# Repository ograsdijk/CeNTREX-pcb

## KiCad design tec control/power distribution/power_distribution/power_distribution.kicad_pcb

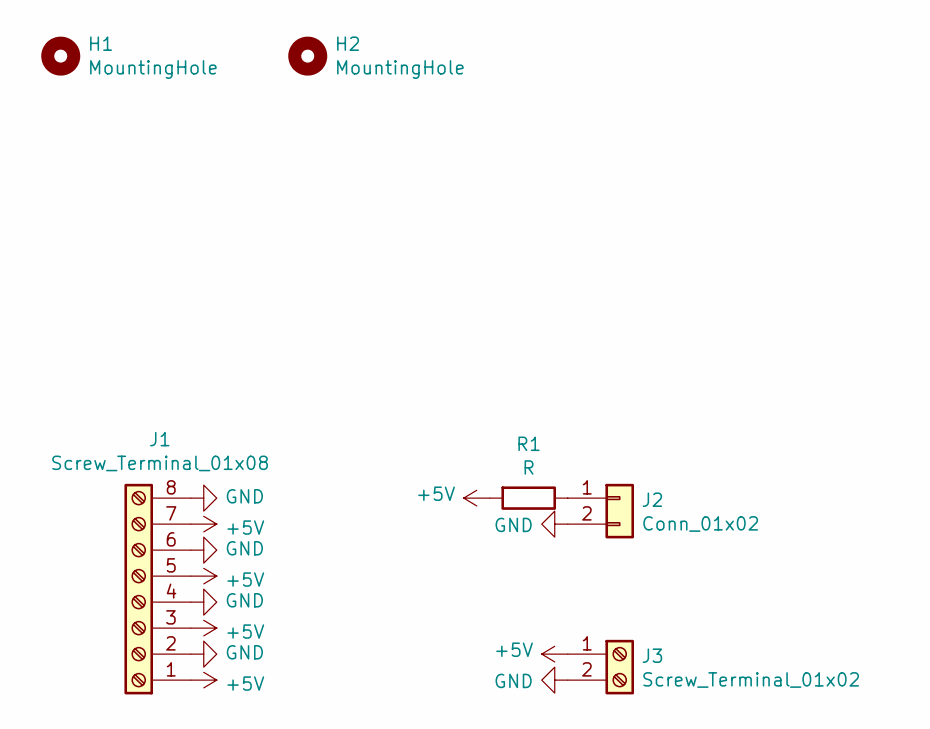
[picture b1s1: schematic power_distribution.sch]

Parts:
H1, H2: MountingHole; MountingHole_2.7mm_M2.5_Pad_Via
J1: Screw_Terminal_01x08; TerminalBlock_RND_205-00018_1x08_P5.00mm_Horizontal
J2: Conn_01x02; PinHeader_1x02_P2.54mm_Vertical
J3: Screw_Terminal_01x02; TerminalBlock_RND_205-00001_1x02_P5.00mm_Horizontal
R1: R; R_Axial_DIN0207_L6.3mm_D2.5mm_P7.62mm_Horizontal

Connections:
+5V: J1.1, J1.3, J1.5, J1.7, J3.1, R1.2
GND: J1.2, J1.4, J1.6, J1.8, J2.2, J3.2
unnamed: J2.1, R1.1

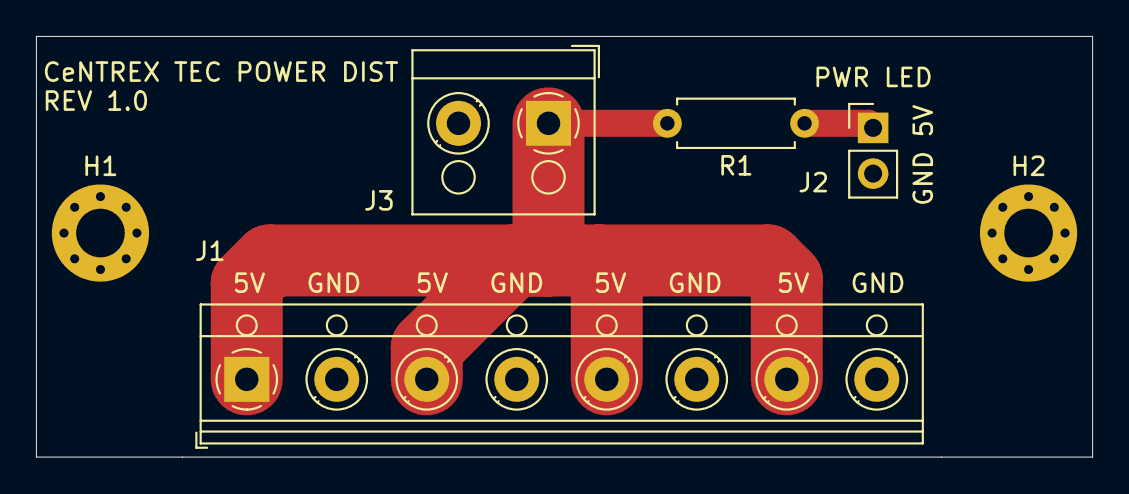
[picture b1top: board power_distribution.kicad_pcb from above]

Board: 2 copper layers, 58.7 x 23.4 mm, 6 parts (0 on the bottom side), 3 nets.

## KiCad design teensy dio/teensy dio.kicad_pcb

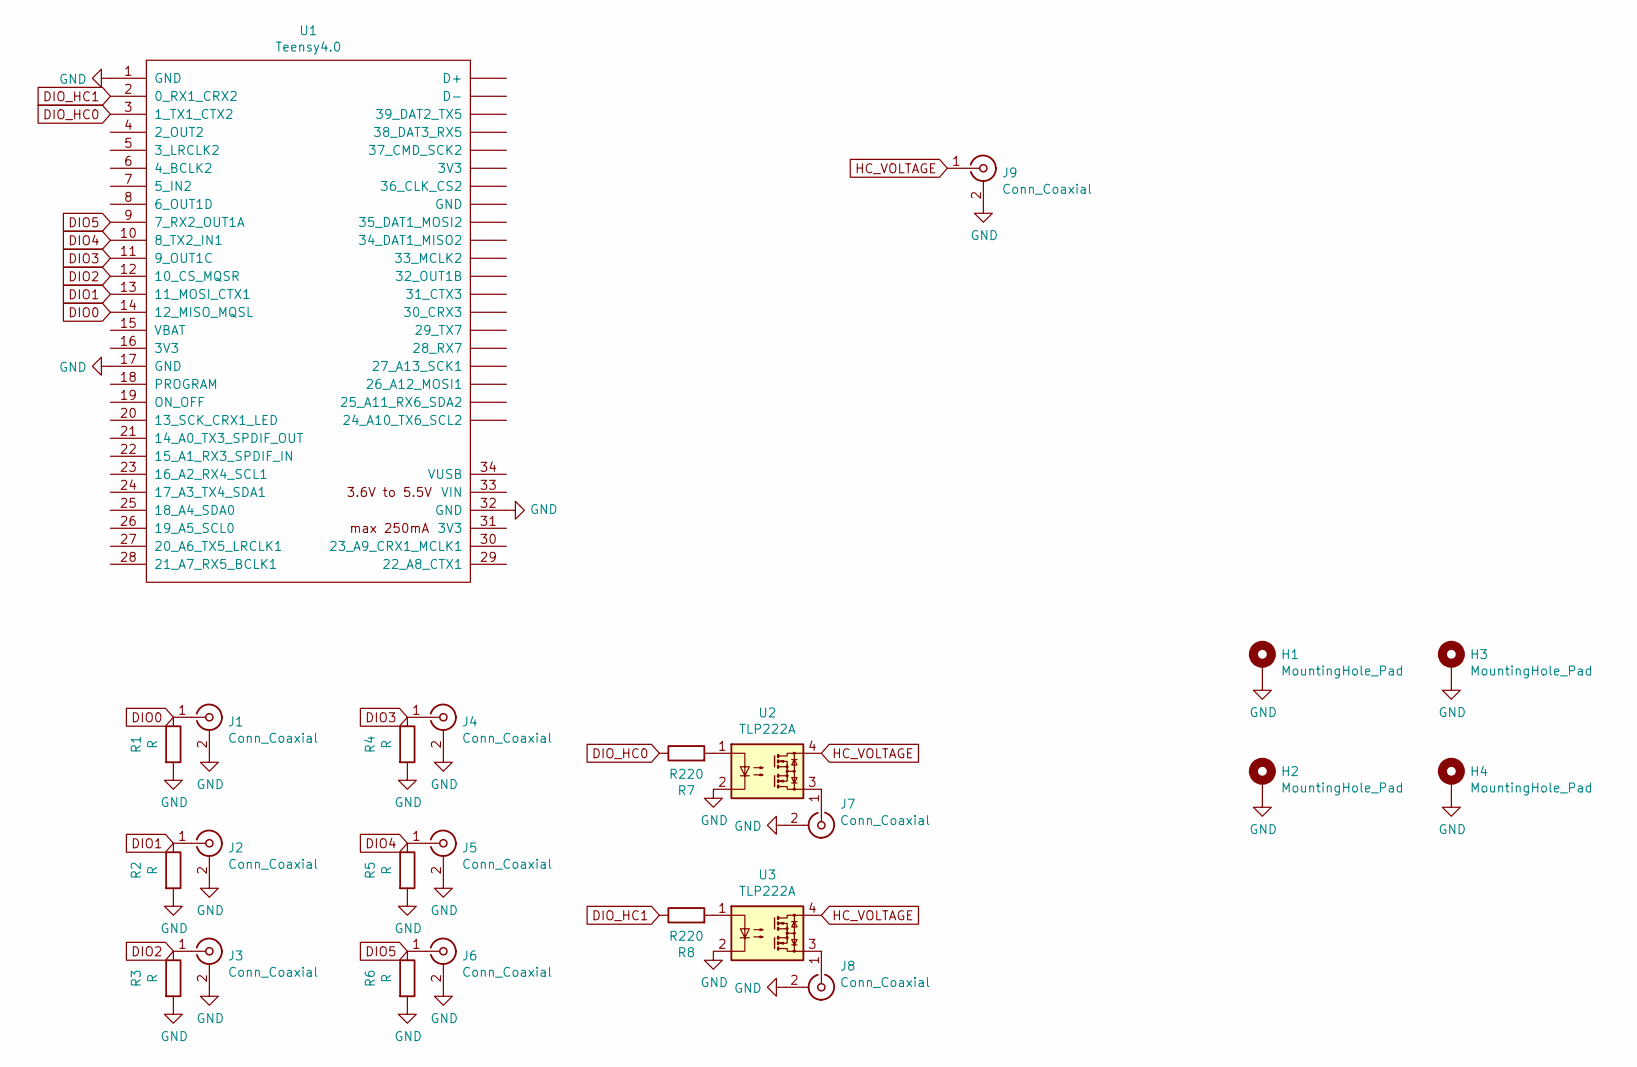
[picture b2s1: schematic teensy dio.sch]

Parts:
H1, H2, H3, H4: MountingHole_Pad; MountingHole_3.2mm_M3_Pad_Via
J1, J2, J3, J4, J5, J6, J7, J8, J9: Conn_Coaxial; BNC_Amphenol_B6252HB-NPP3G-50_Horizontal
R1, R2, R3, R4, R5, R6: R; R_0805_2012Metric
R7, R8: R220; R_0805_2012Metric
U1: Teensy4.0; Teensy40
U2, U3: TLP222A; DIP-4_W7.62mm

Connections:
DIO0: J1.1 (In), R1.1, U1.14 (12_MISO_MQSL)
DIO1: J2.1 (In), R2.1, U1.13 (11_MOSI_CTX1)
DIO2: J3.1 (In), R3.1, U1.12 (10_CS_MQSR)
DIO3: J4.1 (In), R4.1, U1.11 (9_OUT1C)
DIO4: J5.1 (In), R5.1, U1.10 (8_TX2_IN1)
DIO5: J6.1 (In), R6.1, U1.9 (7_RX2_OUT1A)
DIO_HC0: R7.1, U1.3 (1_TX1_CTX2)
DIO_HC1: R8.1, U1.2 (0_RX1_CRX2)
GND: H1.1, H2.1, H3.1, H4.1, J1.2 (Ext), J2.2 (Ext), J3.2 (Ext), J4.2 (Ext), J5.2 (Ext), J6.2 (Ext), J7.2 (Ext), J8.2 (Ext), J9.2 (Ext), R1.2, R2.2, R3.2, R4.2, R5.2, R6.2, U1.1 (GND), U1.17 (GND), U1.32 (GND), U2.2, U3.2
HC_VOLTAGE: J9.1 (In), U2.4, U3.4
unnamed: J7.1 (In), U2.3
unnamed: J8.1 (In), U3.3
unnamed: R7.2, U2.1
unnamed: R8.2, U3.1

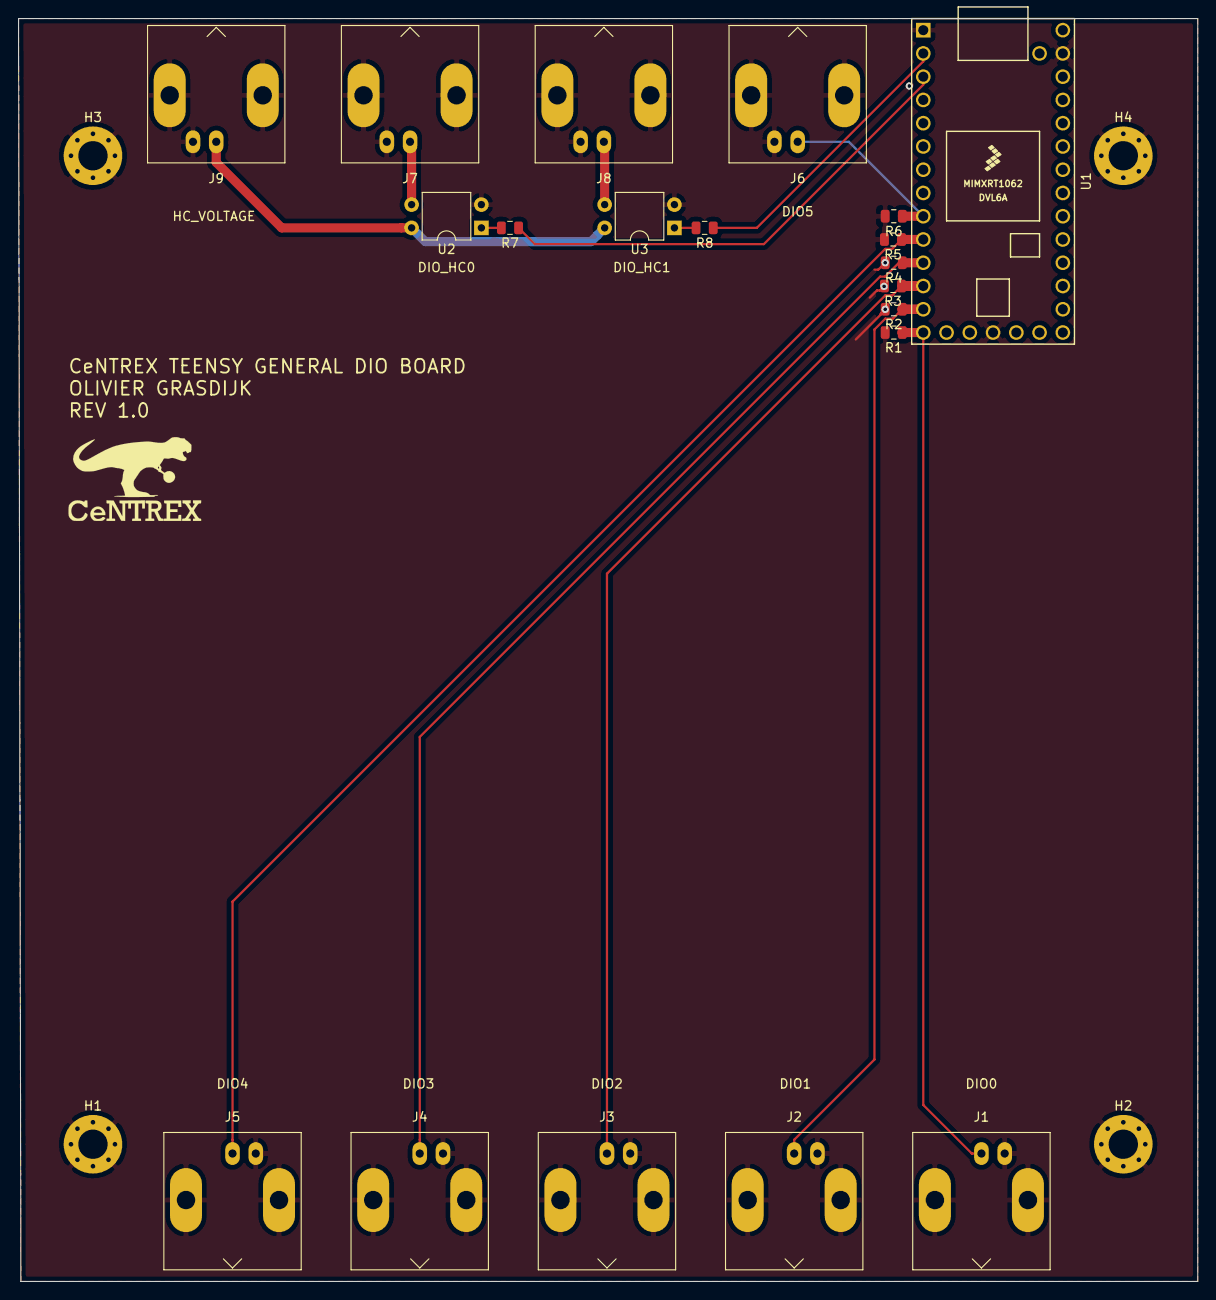
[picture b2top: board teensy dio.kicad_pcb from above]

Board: 2 copper layers, 128.8 x 137.9 mm, 24 parts (0 on the bottom side), 14 nets.

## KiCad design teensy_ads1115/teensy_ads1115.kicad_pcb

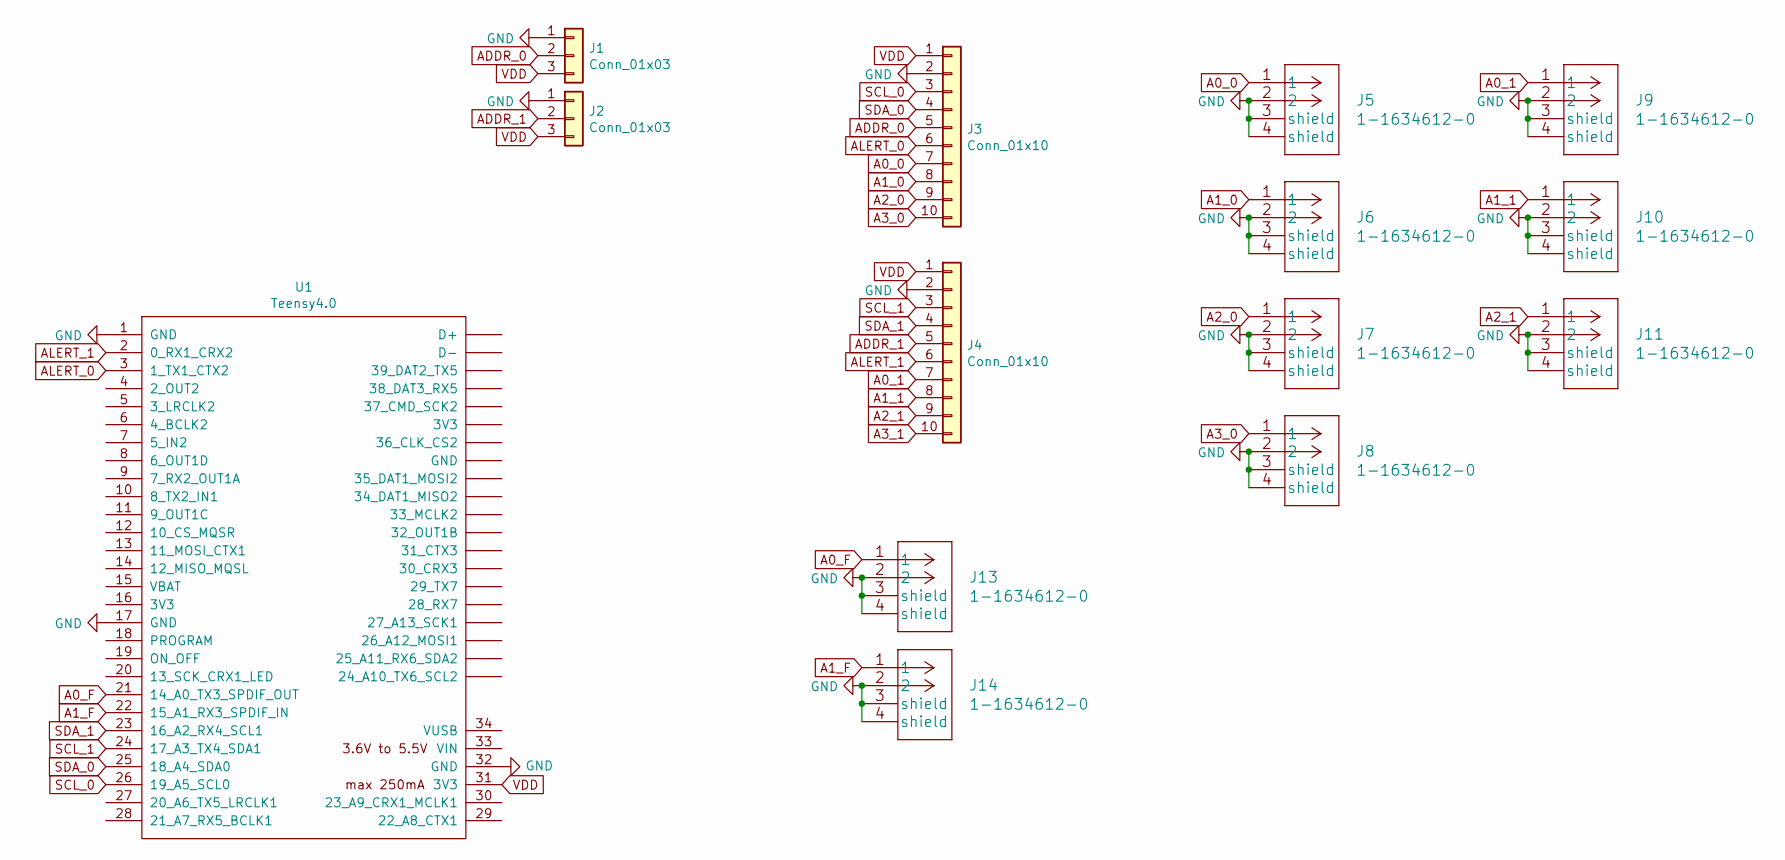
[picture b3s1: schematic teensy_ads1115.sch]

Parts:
J1, J2: Conn_01x03; PinHeader_1x03_P2.54mm_Vertical
J3, J4: Conn_01x10; PinHeader_1x10_P2.54mm_Vertical
J5, J6, J7, J8, J9, J10, J11, J13, J14: 1-1634612-0
U1: Teensy4.0; Teensy40

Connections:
A0_0: J3.7, J5.1
A0_1: J4.7, J9.1
A0_F: J13.1, U1.21 (14_A0_TX3_SPDIF_OUT)
A1_0: J3.8, J6.1
A1_1: J4.8, J10.1
A1_F: J14.1, U1.22 (15_A1_RX3_SPDIF_IN)
A2_0: J3.9, J7.1
A2_1: J4.9, J11.1
A3_0: J3.10, J8.1
A3_1: J4.10
ADDR_0: J1.2, J3.5
ADDR_1: J2.2, J4.5
ALERT_0: J3.6, U1.3 (1_TX1_CTX2)
ALERT_1: J4.6, U1.2 (0_RX1_CRX2)
GND: J1.1, J2.1, J3.2, J4.2, J5.2, J5.3 (shield), J5.4 (shield), J6.2, J6.3 (shield), J6.4 (shield), J7.2, J7.3 (shield), J7.4 (shield), J8.2, J8.3 (shield), J8.4 (shield), J9.2, J9.3 (shield), J9.4 (shield), J10.2, J10.3 (shield), J10.4 (shield), J11.2, J11.3 (shield), J11.4 (shield), J13.2, J13.3 (shield), J13.4 (shield), J14.2, J14.3 (shield), J14.4 (shield), U1.1 (GND), U1.17 (GND), U1.32 (GND)
SCL_0: J3.3, U1.26 (19_A5_SCL0)
SCL_1: J4.3, U1.24 (17_A3_TX4_SDA1)
SDA_0: J3.4, U1.25 (18_A4_SDA0)
SDA_1: J4.4, U1.23 (16_A2_RX4_SCL1)
VDD: J1.3, J2.3, J3.1, J4.1, U1.31 (3V3)

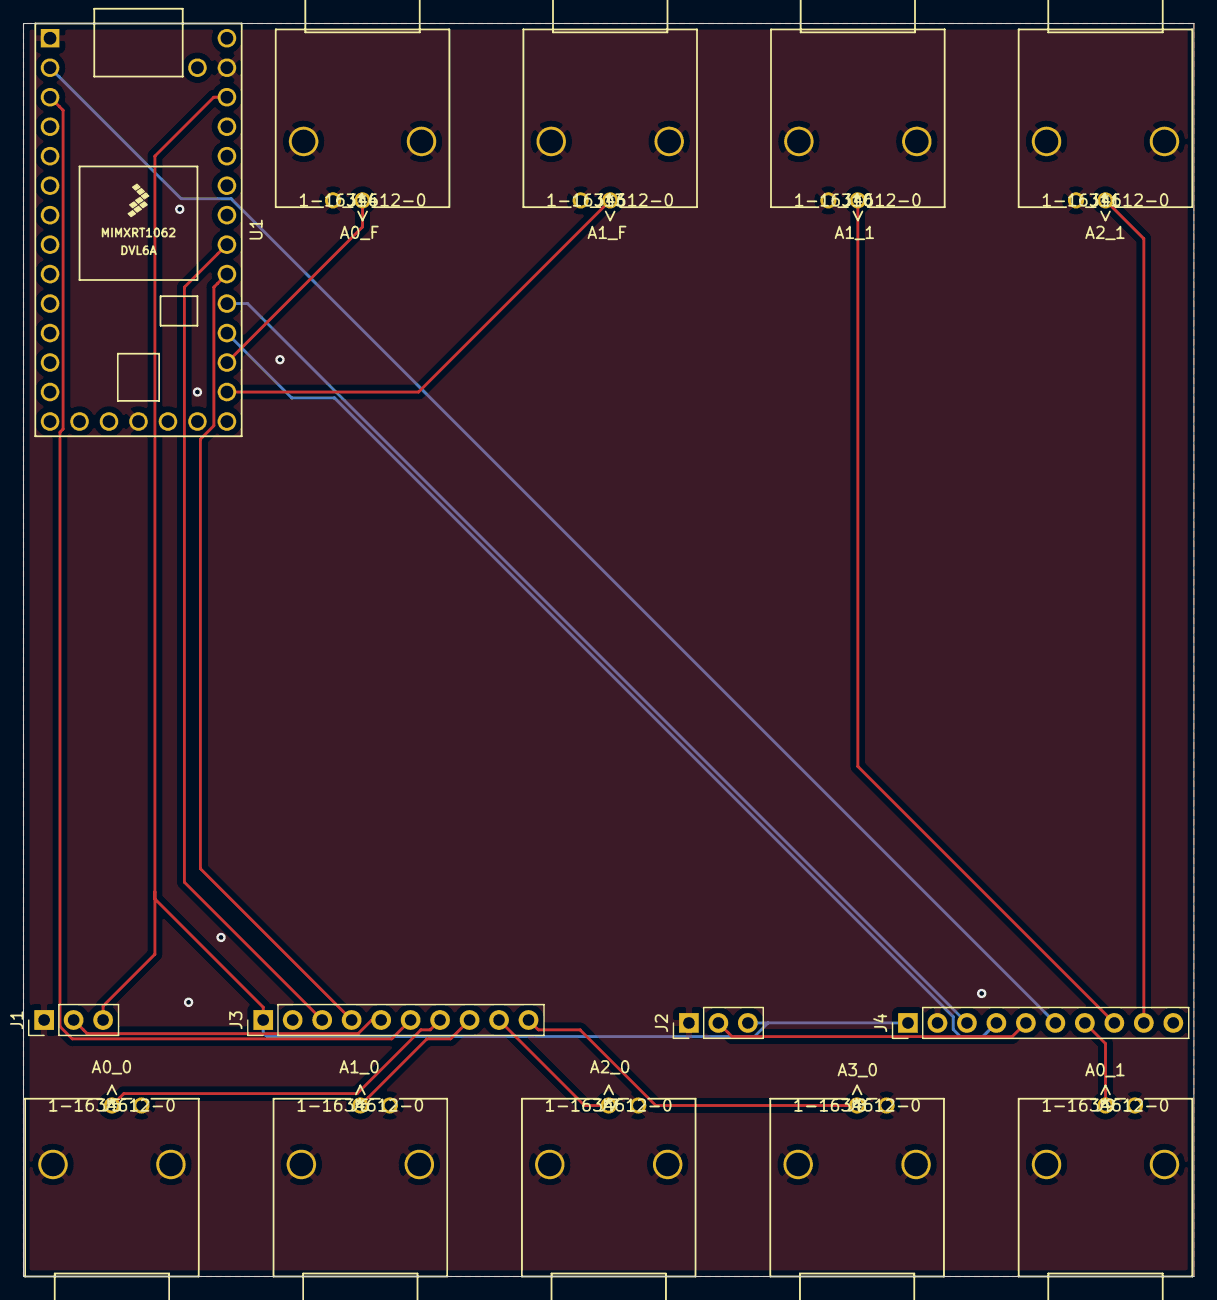
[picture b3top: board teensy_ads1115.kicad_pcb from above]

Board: 2 copper layers, 100.8 x 108.0 mm, 14 parts (0 on the bottom side), 19 nets.

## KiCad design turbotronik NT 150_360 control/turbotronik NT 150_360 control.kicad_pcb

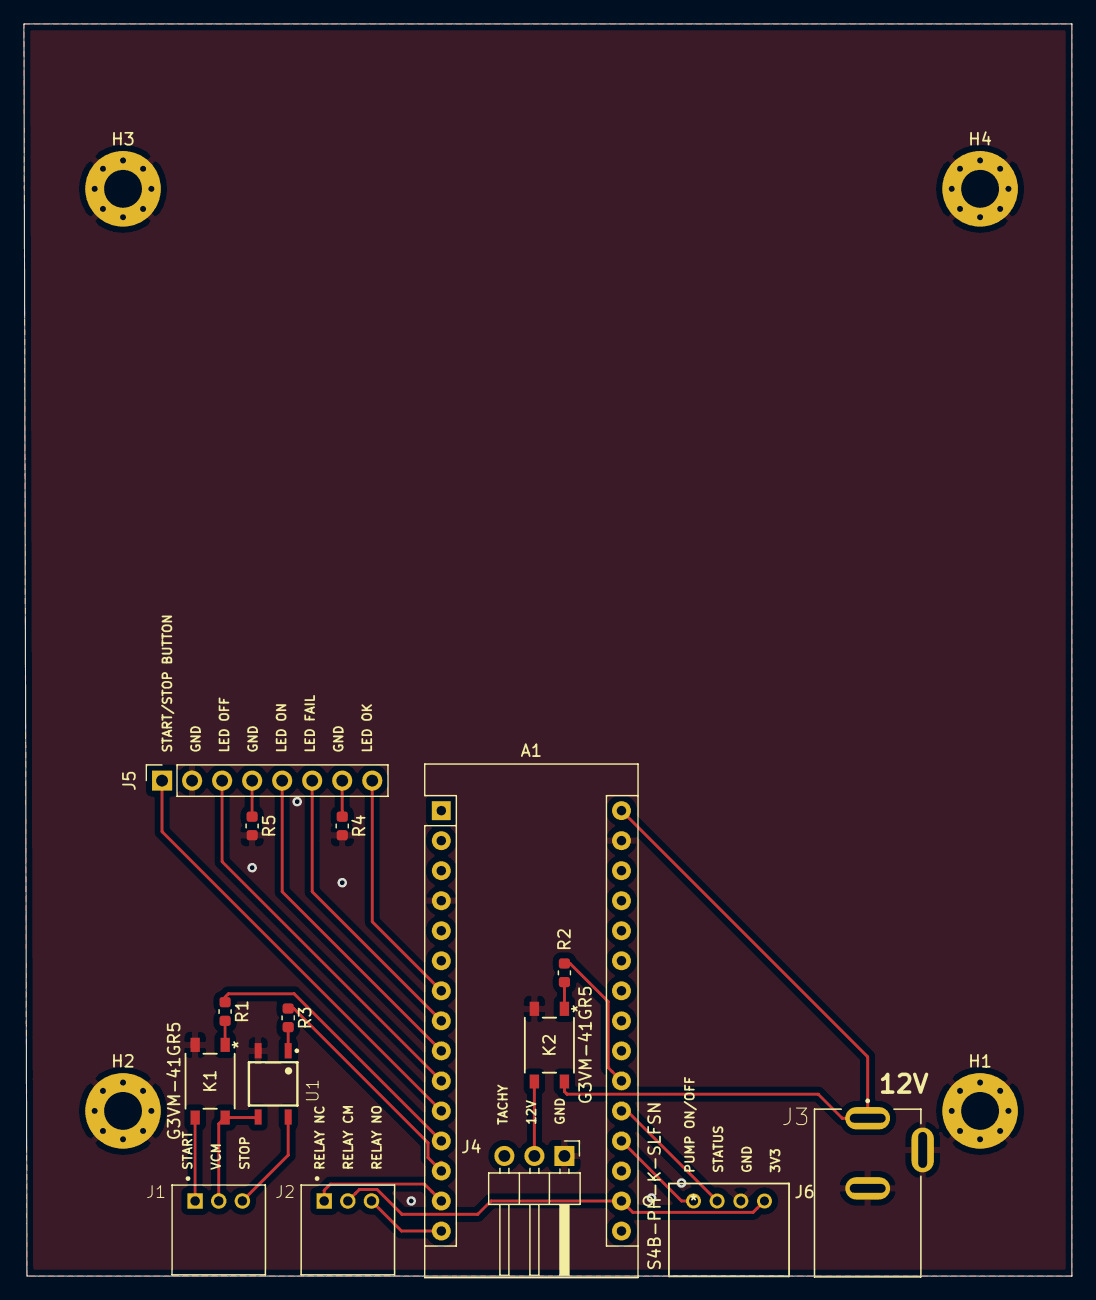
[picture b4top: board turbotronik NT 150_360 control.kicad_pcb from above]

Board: 2 copper layers, 88.6 x 105.9 mm, 19 parts (0 on the bottom side), 24 nets.

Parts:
A1: Arduino_Nano_v3.x; Arduino_Nano
H1, H2, H3, H4: MountingHole_Pad; MountingHole_3.2mm_M3_Pad_Via
J1, J2: S3B-PH-K-S(LF)(SN); JST_S3B-PH-K-S(LF)(SN)
J3: EJ503A; MPD_EJ503A
J4: Conn_01x03; PinHeader_1x03_P2.54mm_Horizontal
J5: Conn_01x08; PinSocket_1x08_P2.54mm_Vertical
J6: S4B-PH-K-SLFSN
K1, K2: G3VM-41GR5
R1, R2, R3, R4, R5: R; R_0603_1608Metric
U1: CPC1117NTR; SOIC254P610X218-4N

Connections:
+12V: A1.30, J3.1, K2.4
FAN: J4.2, K2.3
FAN_DIO: A1.21, R2.1
GND: A1.4, A1.29, H1.1, H2.1, H3.1, H4.1, J3.2, J3.3, J4.1, J5.2, J6.3, K1.2, K2.2, R4.2, R5.2, U1.2
LED_OFF: A1.10, J5.3
LED_ON: A1.9, J5.5
LED_STATUS_FAIL: A1.8, J5.6
LED_STATUS_OK: A1.7, J5.8
unnamed: J5.4, R5.1
unnamed: J5.7, R4.1
unnamed: K1.1, R1.2
unnamed: K2.1, R2.2
unnamed: R3.2, U1.1
PUMP: A1.19, J6.1
PUMP_START: J1.1, K1.3
PUMP_START_DIO: A1.12, R1.1
PUMP_STOP: J1.3, U1.4
PUMP_STOP_DIO: A1.13, R3.1
RELAY_CM: A1.17, J2.2, J6.4
RELAY_NC: A1.14, J2.1
RELAY_NO: A1.15, J2.3
START_STOP_BUTTON: A1.11, J5.1
STATUS: A1.20, J6.2
V_TURBO: J1.2, K1.4, U1.3

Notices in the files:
parts and their libraries:
Copyright 2016 Accelerated Designs. All rights reserved.
